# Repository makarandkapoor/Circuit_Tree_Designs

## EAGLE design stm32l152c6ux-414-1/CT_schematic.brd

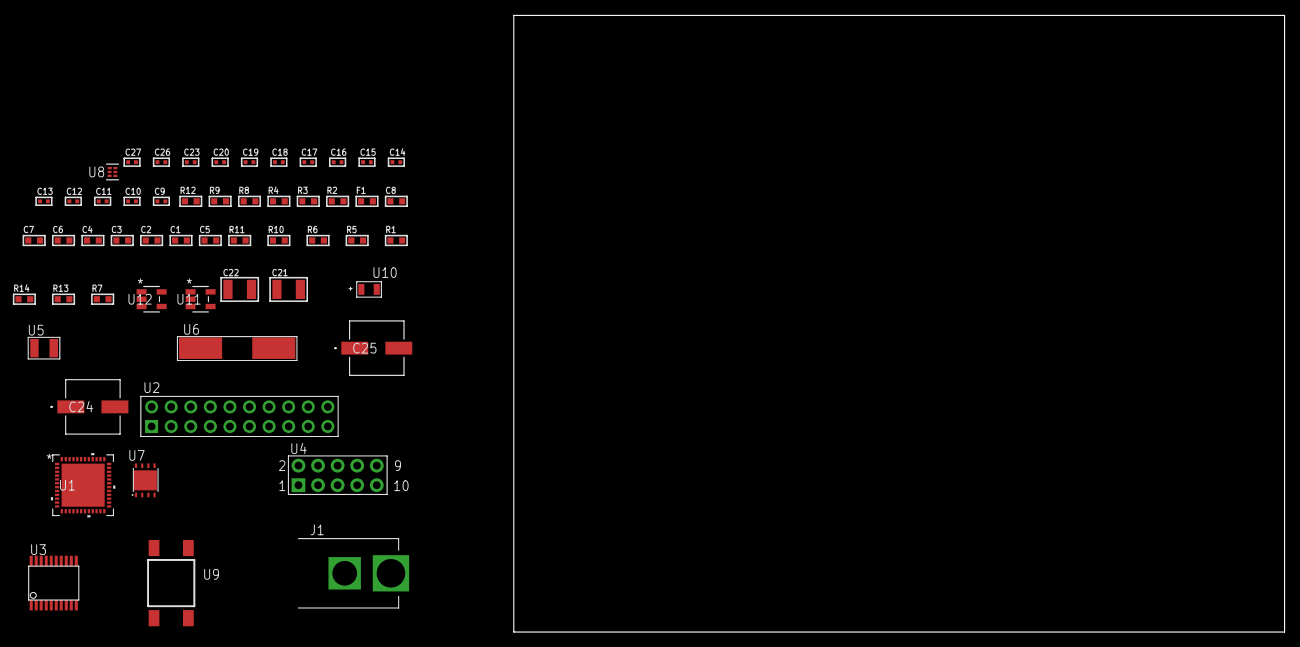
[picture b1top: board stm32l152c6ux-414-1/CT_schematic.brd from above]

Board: 2 copper layers, 100.0 x 80.0 mm, 55 parts (0 on the bottom side), 38 nets, no tracks yet.

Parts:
C1, C2, C3, C4, C6: 1e-07; C0603
C5: 4.7e-06; C0603
C7: 1e-08; C0603
C8: 1e-06; C0603
C9, C10, C11, C12: 1e-11; C0402
C13, C14, C15, C16, C17, C18, C19, C23: 1e-07; C0402
C20, C26, C27: 1e-08; C0402
C21, C22: 1e-05; C1210
C24, C25: 0.0001; EXV-9H
F1: 240.0; L0603
J1: PJ-037B; PJ-037B_PACKAGE
R1, R5, R6, R10, R11: 10000.0; R0603
R2, R9: 1000.0; R0603
R3: 1600.5; R0603
R4: 4700.0; R0603
R7: 100000.0; R0603
R8: 2231.0; R0603
R12: 9100.0; R0603
R13: 680000.0; R0603
R14: 120000.0; R0603
U1: STM32L152C6U6; UFQFPN48
U2: TST-110-05-T-D-RA
U3: SP3203ECY-L/TR; TSSOP20-I
U4: HTSS-105-01-G-D
U5: ABS07-32.768KHZ-7-T
U6: ABLS-25.000MHZ-B2F-T
U7: LP3878SDX-ADJ/NOPB; WSON-8
U8: TPS3895ADRYR; SON-6
U9: 4-1437565-2; SW_4-1437565-2
U10: Q65110A2395; LGM67K-G1J2-24-Z
U11, U12: nc7sz125m5x; NC7SZ125M5X

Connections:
CLK_CRYSTAL_U1_3: C9.1, U1.3, U5.1
CLK_CRYSTAL_U1_4: C10.1, U1.4, U5.2
CLK_CRYSTAL_U1_5: C11.1, U1.5, U6.1
CLK_CRYSTAL_U1_6: C12.1, U1.6, U6.2
GND: C1.2, C2.2, C3.2, C4.2, C5.2, C6.2, C7.2, C8.2, C9.2, C10.2, C11.2, C12.2, C13.2, C14.2, C15.2, C18.2, C19.2, C20.2, C21.2, C22.2, C23.2, C24.2, C25.2, C26.2, C27.2, J1.2, R2.2, R5.2, R9.2, R12.2, R14.2, U1.8, U1.23, U1.35, U1.47, U1.49, U2.4, U2.6, U2.8, U2.10, U2.12, U2.14, U2.16, U2.18, U2.20, U3.18, U4.9, U7.3, U7.PAD, U8.2, U10.C, U11.2, U11.3, U12.1, U12.3
NET_U1_1: C6.1, U1.1
NET_U1_7: R4.1, U1.7, U12.4
NET_U1_9: C7.1, C8.1, F1.1, U1.9
NET_U1_44: R5.1, U1.44
NET_U1_45: R3.1, U1.45, U10.A
NET_U1_46: R1.1, U1.46, U9.3, U9.4
NET_U3_1: C16.1, U3.1
NET_U3_2: C18.1, U3.2
NET_U3_3: C16.2, U3.3
NET_U3_4: C17.1, U3.4
NET_U3_5: C17.2, U3.5
NET_U3_6: C19.1, U3.6
NET_U4_3: U3.14, U4.3
NET_U4_4: U3.13, U4.4
NET_U4_5: U3.17, U4.5
NET_U4_6: U3.16, U4.6
NET_U7_1: C20.1, U7.1
NET_U7_6: R8.2, R9.1, U7.6
NET_U7_8: R7.1, U7.8
NET_U8_1: R11.1, R12.1, U8.1
NET_U8_3: R13.2, R14.1, U8.3
NET_U8_4: R10.1, U8.4, U11.4, U12.2
NET_U9_1: R2.1, U9.1, U9.2
PROC_SYS_JTCK_SWCLK: U1.37, U2.9
PROC_SYS_JTDO_TRACESWO: U1.39, U2.13
PROC_SYS_JTMS_SWDIO: U1.34, U2.7
PROC_USART1_CTS: U1.32, U3.8
PROC_USART1_RTS: U1.33, U3.10
PROC_USART1_RX: U1.31, U3.11
PROC_USART1_TX: U1.30, U3.7
RST_OUT_U2_SRESET_B: R6.1, U2.15, U11.1
VCC_S1_13V5: C21.1, C24.1, C25.1, J1.1, R7.2, U7.4
VCC_TIER1_3V3: C1.1, C2.1, C3.1, C4.1, C5.1, C13.1, C14.1, C15.1, C22.1, C23.1, C26.1, C27.1, F1.2, R1.2, R3.2, R4.2, R6.2, R8.1, R10.2, R11.2, R13.1, U1.24, U1.36, U1.48, U2.1, U3.12, U3.19, U7.5, U8.6, U11.5, U12.5

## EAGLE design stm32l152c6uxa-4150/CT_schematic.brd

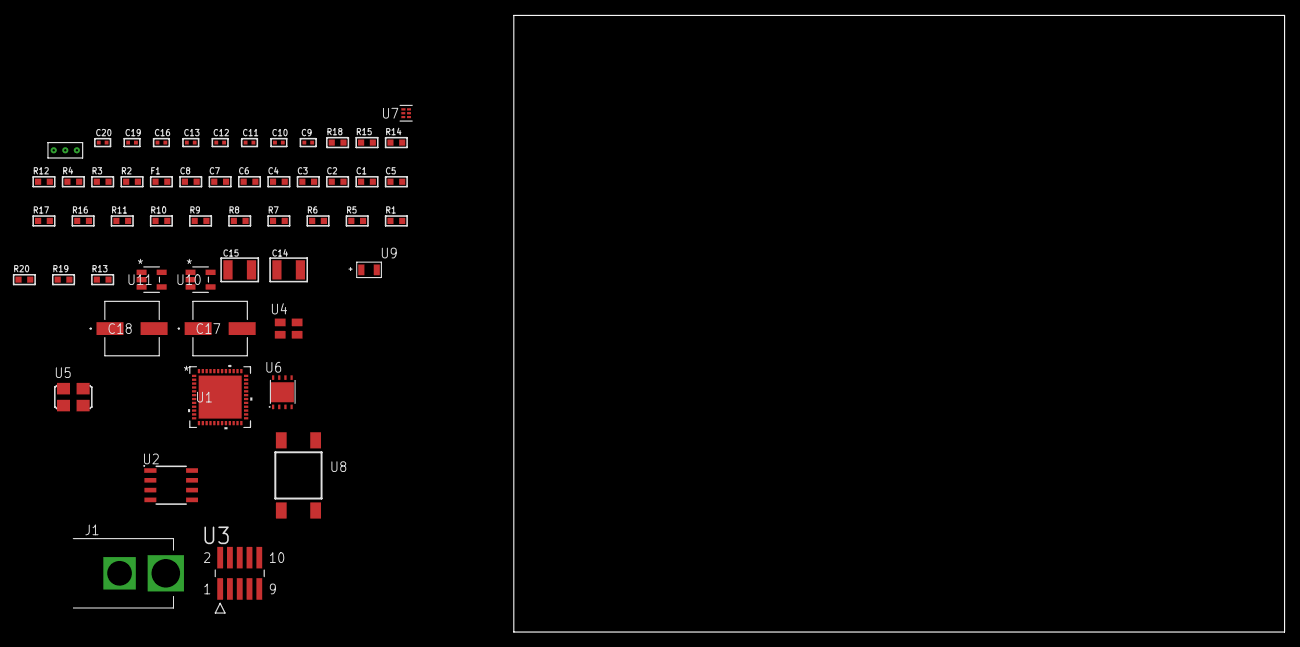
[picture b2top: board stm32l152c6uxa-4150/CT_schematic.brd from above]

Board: 2 copper layers, 100.0 x 80.0 mm, 54 parts (0 on the bottom side), 31 nets, no tracks yet.

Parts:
C1, C2, C3, C4, C6: 1e-07; C0603
C5: 4.7e-06; C0603
C7: 1e-08; C0603
C8: 1e-06; C0603
C9, C11, C12, C13, C19, C20: 1e-08; C0402
C10, C16: 1e-07; C0402
C14, C15: 1e-05; C1210
C17, C18: 0.0001; EXV-9H
F1: 240.0; L0603
J1: PJ-037B; PJ-037B_PACKAGE
R1, R5, R6, R7, R8, R9, R10, R11, R16, R17: 10000.0; R0603
R2, R15: 1000.0; R0603
R3: 1600.5; R0603
R4: 4700.0; R0603
R12: 5.0; R0603
R13: 100000.0; R0603
R14: 2231.0; R0603
R18: 9100.0; R0603
R19: 680000.0; R0603
R20: 120000.0; R0603
U1: STM32L152C6U6A; UFQFPN48
U2: AT25160B-SSHL-T; SOIC-8
U3: FTSH-105-01-L-DV-K; SAMTEC_FTSH-105-01-L-DV-K
U4: ASEK-32.768KHz-ECST; ASEK
U5: ASFL1-25MHZ-NCS; ASFL1
U6: LP3878SDX-ADJ/NOPB; WSON-8
U7: TPS3895ADRYR; SON-6
U8: 4-1437565-2; SW_4-1437565-2
U9: Q65110A2395; LGM67K-G1J2-24-Z
U10, U11: nc7sz125m5x; NC7SZ125M5X
U12: Dummy; DUMMY_PACKAGE_113

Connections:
CLK_U1_3: U1.3, U4.3
CLK_U1_5: U1.5, U5.3
GND: C1.2, C2.2, C3.2, C4.2, C5.2, C6.2, C7.2, C8.2, C9.2, C10.2, C11.2, C12.2, C13.2, C14.2, C15.2, C16.2, C17.2, C18.2, C19.2, C20.2, J1.2, R2.2, R5.2, R12.2, R15.2, R18.2, R20.2, U1.8, U1.23, U1.35, U1.47, U1.49, U2.4, U3.3, U3.5, U4.2, U5.2, U6.3, U6.PAD, U7.2, U9.C, U10.2, U10.3, U11.1, U11.3, U12.1
NET_U1_1: C6.1, U1.1
NET_U1_7: R4.1, U1.7, U11.4
NET_U1_9: C7.1, C8.1, F1.1, U1.9
NET_U1_44: R5.1, U1.44
NET_U1_45: R3.1, U1.45, U9.A
NET_U1_46: R1.1, U1.46, U8.3, U8.4
NET_U2_3: R6.1, U2.3
NET_U2_7: R8.1, U2.7
NET_U3_9: R12.1, U3.9
NET_U6_1: C13.1, U6.1
NET_U6_6: R14.2, R15.1, U6.6
NET_U6_8: R13.1, U6.8
NET_U7_1: R17.1, R18.1, U7.1
NET_U7_3: R19.2, R20.1, U7.3
NET_U7_4: R16.1, U7.4, U10.4, U11.2
NET_U8_1: R2.1, U8.1, U8.2
PROC_ADC_IN19: U1.26, U12.3
PROC_ADC_IN20: U1.27, U12.2
PROC_SPI1_MISO: U1.16, U2.2
PROC_SPI1_MOSI: U1.17, U2.5
PROC_SPI1_NSS: R7.1, U1.14, U2.1
PROC_SPI1_SCK: U1.15, U2.6
PROC_SYS_JTCK_SWCLK: R10.1, U1.37, U3.4
PROC_SYS_JTDO_TRACESWO: U1.39, U3.6
PROC_SYS_JTMS_SWDIO: R11.1, U1.34, U3.2
RST_OUT_U3_JTAG_RST_B: R9.1, U3.10, U10.1
VCC_S1_11V2: C14.1, C17.1, C18.1, J1.1, R13.2, U6.4
VCC_TIER1_3V3: C1.1, C2.1, C3.1, C4.1, C5.1, C9.1, C10.1, C11.1, C12.1, C15.1, C16.1, C19.1, C20.1, F1.2, R1.2, R3.2, R4.2, R6.2, R7.2, R8.2, R9.2, R10.2, R11.2, R14.1, R16.2, R17.2, R19.1, U1.24, U1.36, U1.48, U2.8, U3.1, U4.4, U5.4, U6.5, U7.6, U10.5, U11.5

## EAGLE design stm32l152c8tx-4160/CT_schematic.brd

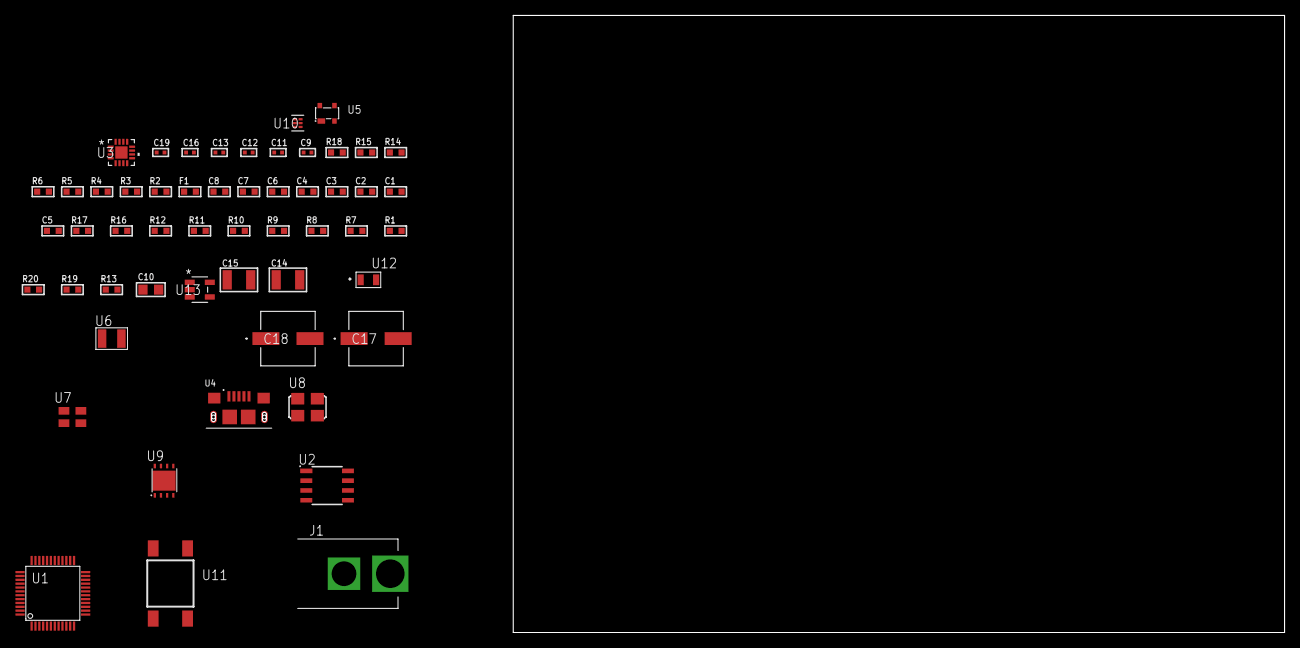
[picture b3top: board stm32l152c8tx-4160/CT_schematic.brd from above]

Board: 2 copper layers, 54 parts (0 on the bottom side), 33 nets, no tracks yet.

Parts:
C1, C2, C3, C4, C6: 1e-07; C0603
C5: 4.7e-06; C0603
C7: 1e-08; C0603
C8: 1e-06; C0603
C9, C11, C12, C13, C19: 1e-08; C0402
C10: 4.7e-06; C0805
C14, C15: 1e-05; C1210
C16: 1e-07; C0402
C17, C18: 0.0001; EXV-9H
F1: 240.0; L0603
J1: PJ-037B; PJ-037B_PACKAGE
R1, R7, R8, R9, R10, R11, R12, R16, R17: 10000.0; R0603
R2, R15: 1000.0; R0603
R3: 1600.5; R0603
R4: 4700.0; R0603
R5, R6: 2200.0; R0603
R13: 100000.0; R0603
R14: 2231.0; R0603
R18: 9100.0; R0603
R19: 680000.0; R0603
R20: 120000.0; R0603
U1: STM32L152C8T6; LQFP48
U2: AT25128B-SSHL-T; SOIC-8
U3: M41T65Q6F; M41T65_QFN-16
U4: 10118193-0001LF; FCI_10118193-0001LF
U5: prtr5v0u2ax; SOT143B
U6: ABS07-32.768KHZ-7-T
U7: ASEK-32.768KHz-ECST; ASEK
U8: ASFL1-25MHZ-NCS; ASFL1
U9: LP3878SDX-ADJ/NOPB; WSON-8
U10: TPS3895ADRYR; SON-6
U11: 4-1437565-2; SW_4-1437565-2
U12: Q65110A2395; LGM67K-G1J2-24-Z
U13: nc7sz125m5x; NC7SZ125M5X

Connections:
CLK_CRYSTAL_U3_1: U3.1, U6.1
CLK_CRYSTAL_U3_2: U3.2, U6.2
CLK_U1_3: U1.3, U7.3
CLK_U1_5: U1.5, U8.3
GND: C1.2, C2.2, C3.2, C4.2, C5.2, C6.2, C7.2, C8.2, C9.2, C10.2, C11.2, C12.2, C13.2, C14.2, C15.2, C16.2, C17.2, C18.2, C19.2, J1.2, R2.2, R7.2, R15.2, R18.2, R20.2, U1.8, U1.23, U1.35, U1.47, U2.4, U3.3, U3.5, U3.17, U4.5, U4.6, U4.7, U4.8, U4.9, U5.1, U7.2, U8.2, U9.3, U9.PAD, U10.2, U12.C, U13.1, U13.3
NET_U1_1: C6.1, U1.1
NET_U1_7: R4.1, U1.7, U13.4
NET_U1_9: C7.1, C8.1, F1.1, U1.9
NET_U1_42: R5.1, U1.42, U3.10
NET_U1_43: R6.1, U1.43, U3.9
NET_U1_44: R7.1, U1.44
NET_U1_45: R3.1, U1.45, U12.A
NET_U1_46: R1.1, U1.46, U11.3, U11.4
NET_U2_3: R8.1, U2.3
NET_U2_7: R10.1, U2.7
NET_U3_4: R11.1, U3.4
NET_U3_11: R12.1, U3.11
NET_U5_4: U4.1, U5.4
NET_U9_1: C13.1, U9.1
NET_U9_6: R14.2, R15.1, U9.6
NET_U9_8: R13.1, U9.8
NET_U10_1: R17.1, R18.1, U10.1
NET_U10_3: R19.2, R20.1, U10.3
NET_U10_4: R16.1, U10.4, U13.2
NET_U11_1: R2.1, U11.1, U11.2
PROC_SPI1_MISO: U1.16, U2.2
PROC_SPI1_MOSI: U1.17, U2.5
PROC_SPI1_NSS: R9.1, U1.14, U2.1
PROC_SPI1_SCK: U1.15, U2.6
PROC_USB_DM: U1.32, U4.2, U5.3
PROC_USB_DP: U1.33, U4.3, U5.2
VCC_S1_11V3: C14.1, C17.1, C18.1, J1.1, R13.2, U9.4
VCC_TIER1_3V3: C1.1, C2.1, C3.1, C4.1, C5.1, C9.1, C10.1, C11.1, C12.1, C15.1, C16.1, C19.1, F1.2, R1.2, R3.2, R4.2, R5.2, R6.2, R8.2, R9.2, R10.2, R11.2, R12.2, R14.1, R16.2, R17.2, R19.1, U1.24, U1.36, U1.48, U2.8, U3.14, U7.4, U8.4, U9.5, U10.6, U13.5

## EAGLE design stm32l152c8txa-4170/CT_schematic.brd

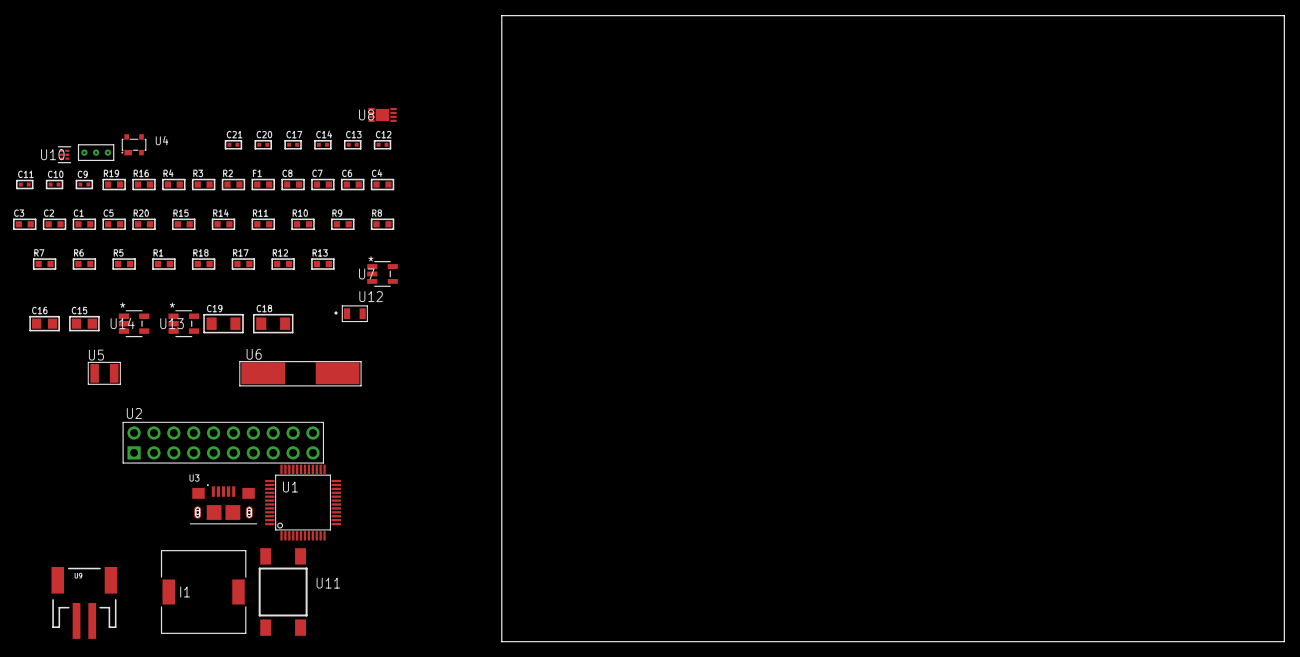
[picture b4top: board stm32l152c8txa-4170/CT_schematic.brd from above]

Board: 2 copper layers, 58 parts (0 on the bottom side), 34 nets, no tracks yet.

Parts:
C1, C2, C3, C4, C6: 1e-07; C0603
C5: 4.7e-06; C0603
C7: 1e-08; C0603
C8: 1e-06; C0603
C9, C10, C11, C12: 1e-11; C0402
C13, C14, C17: 1e-07; C0402
C15, C16: 1e-05; C0805
C18, C19: 1e-05; C1206
C20, C21: 1e-08; C0402
F1: 240.0; L0603
I1: 3.8e-06; DR1040
R1, R5, R6, R7, R8, R9, R10, R11, R14, R15, R20: 10000.0; R0603
R2: 1000.0; R0603
R3: 1600.5; R0603
R4: 4700.0; R0603
R12: 220000.0; R0603
R13: 1000000.0; R0603
R16: 9100.0; R0603
R17: 680000.0; R0603
R18: 120000.0; R0603
R19: 2000.0; R0603
U1: STM32L152C8T6A; LQFP48
U2: TST-110-05-T-D-RA
U3: 10118193-0001LF; FCI_10118193-0001LF
U4: prtr5v0u2ax; SOT143B
U5: ABS07-32.768KHZ-7-T
U6: ABLS-25.000MHZ-B2F-T
U7: ltc3406es5; TSOT-23-5
U8: MCP73831T-2ACI/MC; DFN8_2X3MC
U9: S2B-PH-SM4-TB(LF)(SN); JST-2-SMD
U10: TPS3895ADRYR; SON-6
U11: 4-1437565-2; SW_4-1437565-2
U12: Q65110A2395; LGM67K-G1J2-24-Z
U13, U14: nc7sz125m5x; NC7SZ125M5X
U15: Dummy; DUMMY_PACKAGE_119

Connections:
CLK_CRYSTAL_U1_3: C9.1, U1.3, U5.1
CLK_CRYSTAL_U1_4: C10.1, U1.4, U5.2
CLK_CRYSTAL_U1_5: C11.1, U1.5, U6.1
CLK_CRYSTAL_U1_6: C12.1, U1.6, U6.2
GND: C1.2, C2.2, C3.2, C4.2, C5.2, C6.2, C7.2, C8.2, C9.2, C10.2, C11.2, C12.2, C13.2, C14.2, C15.2, C16.1, C16.2, C17.2, C18.2, C19.2, C20.2, C21.2, R2.2, R5.2, R11.2, R12.2, R16.2, R18.2, R19.2, U1.8, U1.23, U1.35, U1.47, U2.4, U2.6, U2.8, U2.10, U2.12, U2.14, U2.16, U2.18, U2.20, U3.5, U3.6, U3.7, U3.8, U3.9, U4.1, U7.2, U8.6, U8.9, U9.2, U10.2, U12.C, U13.2, U13.3, U14.1, U14.3, U15.1
INPUT_USBPOWER_5V: C18.1, R20.2, U3.1, U4.4, U8.1, U8.2
NET_U1_1: C6.1, U1.1
NET_U1_7: R4.1, U1.7, U14.4
NET_U1_9: C7.1, C8.1, F1.1, U1.9
NET_U1_44: R5.1, U1.44
NET_U1_45: R3.1, U1.45, U12.A
NET_U1_46: R1.1, U1.46, U11.3, U11.4
NET_U2_19: R11.1, U2.19
NET_U7_3: I1.1, U7.3
NET_U7_5: R12.1, R13.1, U7.5
NET_U7_ATNET_3: I1.2, R13.2
NET_U8_5: R20.1, U8.5
NET_U8_8: R19.1, U8.8
NET_U10_1: R15.1, R16.1, U10.1
NET_U10_3: R17.2, R18.1, U10.3
NET_U10_4: R14.1, U10.4, U13.4, U14.2
NET_U11_1: R2.1, U11.1, U11.2
PROC_SYS_JTCK_SWCLK: R9.1, U1.37, U2.9
PROC_SYS_JTDI: R7.1, U1.38, U2.5
PROC_SYS_JTDO_TRACESWO: U1.39, U2.13
PROC_SYS_JTMS_SWDIO: R8.1, U1.34, U2.7
PROC_SYS_JTRST: R6.1, U1.40, U2.3
PROC_TIM10_CH1: U1.16, U15.2
PROC_TIM11_CH1: U1.17, U15.3
PROC_USB_DM: U1.32, U3.2, U4.3
PROC_USB_DP: U1.33, U3.3, U4.2
RST_OUT_U2_SRESET_B: R10.1, U2.15, U13.1
VCC_S1_3V7: C15.1, C19.1, U7.4, U8.3, U8.4, U9.1
VCC_TIER1_3V3: C1.1, C2.1, C3.1, C4.1, C5.1, C13.1, C14.1, C16.2, C17.1, C20.1, C21.1, F1.2, I1.2, R1.2, R3.2, R4.2, R6.2, R7.2, R8.2, R9.2, R10.2, R13.2, R14.2, R15.2, R17.1, U1.24, U1.36, U1.48, U2.1, U2.2, U10.6, U13.5, U14.5

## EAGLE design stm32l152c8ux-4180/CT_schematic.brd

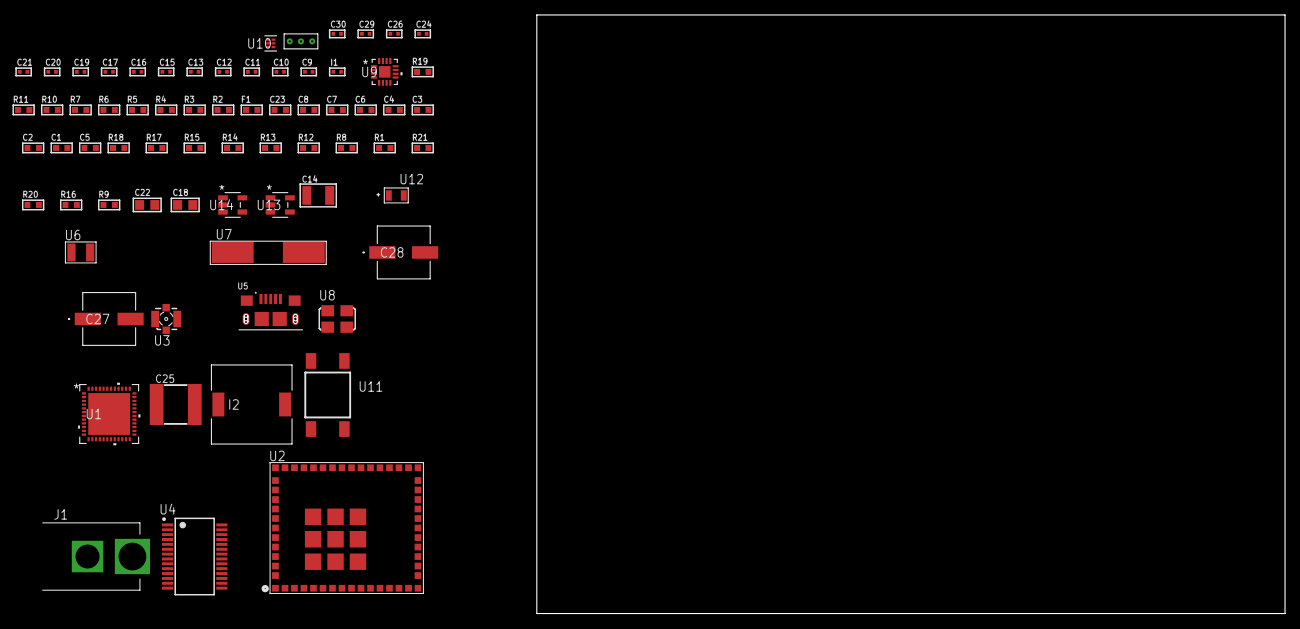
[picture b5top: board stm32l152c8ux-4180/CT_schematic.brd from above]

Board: 2 copper layers, 70 parts (0 on the bottom side), 42 nets, no tracks yet.

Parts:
C1, C2, C3, C4, C6: 1e-07; C0603
C5: 4.7e-06; C0603
C7: 1e-08; C0603
C8, C23: 1e-06; C0603
C9, C10, C11, C12: 1e-11; C0402
C13: 1e-12; C0402
C14: 2.2e-05; C1210
C15, C16, C17, C19, C20, C24, C26: 1e-07; C0402
C18: 4.7e-06; C0805
C21, C29, C30: 1e-08; C0402
C22: 1e-05; C0805
C25: 6.8e-05; 2220
C27, C28: 0.0001; EXV-9H
F1: 240.0; L0603
I1: 3.6e-09; C0402
I2: 5.2e-06; DR1040
J1: PJ-037B; PJ-037B_PACKAGE
R1, R8, R12, R13, R17, R18: 10000.0; R0603
R2: 1000.0; R0603
R3: 1600.5; R0603
R4, R5, R11: 4700.0; R0603
R6, R7: 2200.0; R0603
R9: 100000.0; R0603
R10: 2700.0; R0603
R14: 20000.0; R0603
R15: 91000.0; R0603
R16: 300000.0; R0603
R19: 9100.0; R0603
R20: 680000.0; R0603
R21: 120000.0; R0603
U1: STM32L152C8U6; UFQFPN48
U2: CC3200MODR1M2AMOBT; LGA63S127P16X13_2050X1750X150
U3: 73412-0114; COAXIAL_C
U4: FT232RL-REEL; SSOP-28
U5: 10118193-0001LF; FCI_10118193-0001LF
U6: ABS07-32.768KHZ-7-T
U7: ABLS-25.000MHZ-B2F-T
U8: ASFL1-12MHZ-NCS; ASFL1
U9: LTC3601EUD#PBF; QFN-16_EP
U10: TPS3895ADRYR; SON-6
U11: 4-1437565-2; SW_4-1437565-2
U12: Q65110A2395; LGM67K-G1J2-24-Z
U13, U14: nc7sz125m5x; NC7SZ125M5X
U15: Dummy; DUMMY_PACKAGE_144

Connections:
CLK_CRYSTAL_U1_3: C9.1, U1.3, U6.1
CLK_CRYSTAL_U1_4: C10.1, U1.4, U6.2
CLK_CRYSTAL_U1_5: C11.1, U1.5, U7.1
CLK_CRYSTAL_U1_6: C12.1, U1.6, U7.2
CLK_U4_27: U4.27, U8.3
GND: C1.2, C2.2, C3.2, C4.2, C5.2, C6.2, C7.2, C8.2, C9.2, C10.2, C11.2, C12.2, C13.2, C14.2, C15.2, C16.2, C17.2, C18.2, C19.2, C20.2, C21.2, C22.2, C23.2, C25.1, C25.2, C26.2, C27.2, C28.2, C29.2, C30.2, J1.2, R2.2, R8.2, R9.2, R10.2, R13.2, R14.2, R16.2, R19.2, R21.2, U1.8, U1.23, U1.35, U1.47, U1.49, U2.1, U2.2, U2.16, U2.27, U2.28, U2.30, U2.32, U2.38, U2.43, U2.55, U2.56, U2.57, U2.58, U2.59, U2.60, U2.61, U2.62, U2.63, U3.1, U3.2, U3.3, U3.4, U4.7, U4.18, U4.21, U4.25, U4.26, U5.5, U5.6, U5.7, U5.8, U5.9, U8.2, U9.1, U9.9, U9.17, U10.2, U12.C, U13.1, U13.3, U14.1, U14.3, U15.1
NET_U1_1: C6.1, U1.1
NET_U1_7: R5.1, U1.7, U14.4
NET_U1_9: C7.1, C8.1, F1.1, U1.9
NET_U1_42: R6.1, U1.42, U2.3
NET_U1_43: R7.1, U1.43, U2.4
NET_U1_44: R8.1, U1.44
NET_U1_45: R3.1, U1.45, U12.A
NET_U1_46: R1.1, U1.46, U11.3, U11.4
NET_U2_21: R9.1, U2.21
NET_U2_23: R10.1, U2.23
NET_U2_35: R4.1, U2.35, U13.4
NET_U3_1: C13.1, I1.1, U3.1
NET_U4_14: R12.1, U4.14
NET_U4_17: C19.1, U4.17
NET_U4_19: R13.1, U4.19
NET_U5_1: R11.1, U5.1
NET_U5_2: U4.16, U5.2
NET_U5_3: U4.15, U5.3
NET_U9_3: C24.2, I2.1, U9.3, U9.4
NET_U9_6: C24.1, U9.6
NET_U9_7: C23.1, U9.7, U9.12
NET_U9_10: R16.1, U9.10
NET_U9_11: R14.1, R15.1, U9.11
NET_U9_ATNET_3: I2.2, R15.2
NET_U10_1: R18.1, R19.1, U10.1
NET_U10_3: R20.2, R21.1, U10.3
NET_U10_4: R17.1, U10.4, U13.2, U14.2
NET_U11_1: R2.1, U11.1, U11.2
PROC_ADC_IN19: U1.26, U15.3
PROC_ADC_IN20: U1.27, U15.2
PROC_USART1_CTS: U1.32, U4.3
PROC_USART1_RTS: U1.33, U4.11
PROC_USART1_RX: U1.31, U4.1
PROC_USART1_TX: U1.30, U4.5
VCC_S1_11V2: C22.1, C27.1, C28.1, J1.1, U9.15, U9.16
VCC_TIER1_3V3: C1.1, C2.1, C3.1, C4.1, C5.1, C14.1, C15.1, C16.1, C17.1, C18.1, C20.1, C21.1, C25.2, C26.1, C29.1, C30.1, F1.2, I2.2, R1.2, R3.2, R4.2, R5.2, R6.2, R7.2, R12.2, R15.2, R17.2, R18.2, R20.1, U1.24, U1.36, U1.48, U2.36, U2.37, U2.40, U4.4, U4.20, U8.4, U9.8, U10.6, U13.5, U14.5

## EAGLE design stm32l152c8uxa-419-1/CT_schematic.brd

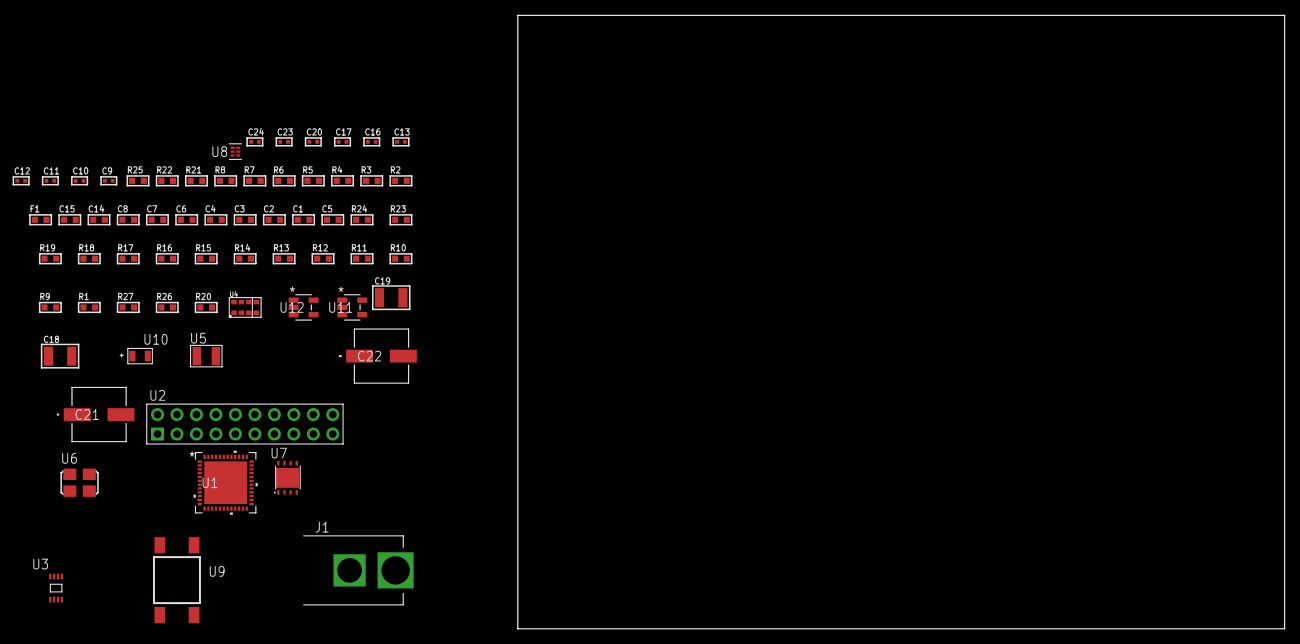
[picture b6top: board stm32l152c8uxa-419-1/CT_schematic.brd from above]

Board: 2 copper layers, 100.0 x 80.0 mm, 65 parts (0 on the bottom side), 34 nets, no tracks yet.

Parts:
C1, C2, C3, C4, C6: 1e-07; C0603
C5: 4.7e-06; C0603
C7: 1e-08; C0603
C8, C14, C15: 1e-06; C0603
C9, C10: 1e-11; C0402
C11, C12, C20: 1e-07; C0402
C13, C16, C17, C23, C24: 1e-08; C0402
C18, C19: 1e-05; C1210
C21, C22: 0.0001; EXV-9H
F1: 240.0; L0603
J1: PJ-037B; PJ-037B_PACKAGE
R1, R9, R10, R11, R12, R13, R14, R15, R16, R17, R18, R19, R23, R24: 10000.0; R0603
R2, R22: 1000.0; R0603
R3: 1600.5; R0603
R4: 4700.0; R0603
R5, R6, R7, R8: 2200.0; R0603
R20: 100000.0; R0603
R21: 2231.0; R0603
R25: 9100.0; R0603
R26: 680000.0; R0603
R27: 120000.0; R0603
U1: STM32L152C8U6A; UFQFPN48
U2: TST-110-05-T-D-RA
U3: 24AA128T-I/MNY; TDFN-8/6MM
U4: TMD27711; SMD-8
U5: ABS07-32.768KHZ-7-T
U6: ASFL1-25MHZ-NCS; ASFL1
U7: LP3878SDX-ADJ/NOPB; WSON-8
U8: TPS3895ADRYR; SON-6
U9: 4-1437565-2; SW_4-1437565-2
U10: Q65110A2395; LGM67K-G1J2-24-Z
U11, U12: nc7sz125m5x; NC7SZ125M5X

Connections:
CLK_CRYSTAL_U1_3: C9.1, U1.3, U5.1
CLK_CRYSTAL_U1_4: C10.1, U1.4, U5.2
CLK_U1_5: U1.5, U6.3
GND: C1.2, C2.2, C3.2, C4.2, C5.2, C6.2, C7.2, C8.2, C9.2, C10.2, C11.2, C12.2, C13.2, C14.2, C15.2, C16.2, C17.2, C18.2, C19.2, C20.2, C21.2, C22.2, C23.2, C24.2, J1.2, R2.2, R9.2, R15.2, R17.2, R18.2, R22.2, R25.2, R27.2, U1.8, U1.23, U1.35, U1.47, U1.49, U2.4, U2.6, U2.8, U2.10, U2.12, U2.14, U2.16, U2.18, U2.20, U3.4, U3.7, U4.3, U6.2, U7.3, U7.PAD, U8.2, U10.C, U11.2, U11.3, U12.1, U12.3
NET_U1_1: C6.1, U1.1
NET_U1_7: R4.1, U1.7, U12.4
NET_U1_9: C7.1, C8.1, F1.1, U1.9
NET_U1_21: R7.1, U1.21, U3.6
NET_U1_22: R8.1, U1.22, U3.5
NET_U1_42: R5.1, U1.42, U4.2
NET_U1_43: R6.1, U1.43, U4.8
NET_U1_44: R9.1, U1.44
NET_U1_45: R3.1, U1.45, U10.A
NET_U1_46: R1.1, U1.46, U9.3, U9.4
NET_U2_19: R15.1, U2.19
NET_U3_1: R16.1, U3.1
NET_U3_2: R17.1, U3.2
NET_U3_3: R18.1, U3.3
NET_U4_7: R19.1, U4.7
NET_U7_1: C17.1, U7.1
NET_U7_6: R21.2, R22.1, U7.6
NET_U7_8: R20.1, U7.8
NET_U8_1: R24.1, R25.1, U8.1
NET_U8_3: R26.2, R27.1, U8.3
NET_U8_4: R23.1, U8.4, U11.4, U12.2
NET_U9_1: R2.1, U9.1, U9.2
PROC_SYS_JTCK_SWCLK: R13.1, U1.37, U2.9
PROC_SYS_JTDI: R11.1, U1.38, U2.5
PROC_SYS_JTDO_TRACESWO: U1.39, U2.13
PROC_SYS_JTMS_SWDIO: R12.1, U1.34, U2.7
PROC_SYS_JTRST: R10.1, U1.40, U2.3
RST_OUT_U2_SRESET_B: R14.1, U2.15, U11.1
VCC_S1_12V5: C18.1, C21.1, C22.1, J1.1, R20.2, U7.4
VCC_TIER1_3V3: C1.1, C2.1, C3.1, C4.1, C5.1, C11.1, C12.1, C13.1, C14.1, C15.1, C16.1, C19.1, C20.1, C23.1, C24.1, F1.2, R1.2, R3.2, R4.2, R5.2, R6.2, R7.2, R8.2, R10.2, R11.2, R12.2, R13.2, R14.2, R16.2, R19.2, R21.1, R23.2, R24.2, R26.1, U1.24, U1.36, U1.48, U2.1, U2.2, U3.8, U4.1, U4.4, U6.4, U7.5, U8.6, U11.5, U12.5

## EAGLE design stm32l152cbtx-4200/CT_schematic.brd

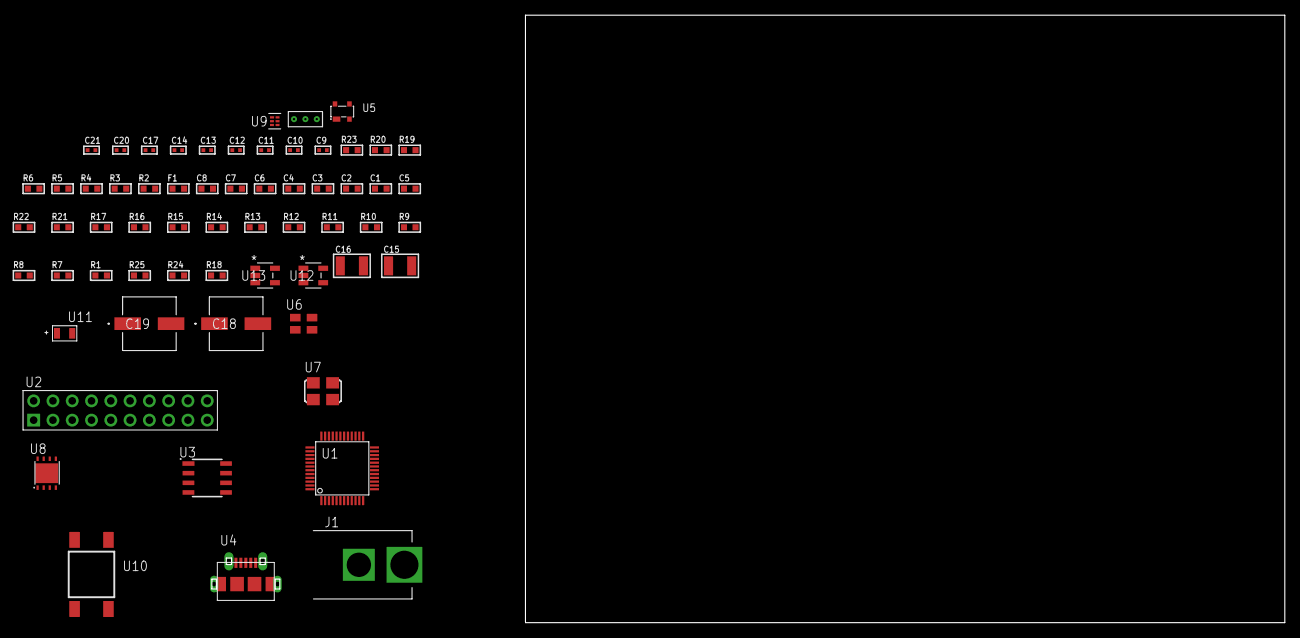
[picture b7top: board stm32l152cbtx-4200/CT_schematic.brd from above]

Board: 2 copper layers, 62 parts (0 on the bottom side), 36 nets, no tracks yet.

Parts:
C1, C2, C3, C4, C6: 1e-07; C0603
C5: 4.7e-06; C0603
C7: 1e-08; C0603
C8: 1e-06; C0603
C9, C10, C17: 1e-07; C0402
C11, C12, C13, C14, C20, C21: 1e-08; C0402
C15, C16: 1e-05; C1210
C18, C19: 0.0001; EXV-9H
F1: 240.0; L0603
J1: PJ-037B; PJ-037B_PACKAGE
R1, R7, R8, R9, R10, R11, R12, R13, R14, R15, R16, R17, R21, R22: 10000.0; R0603
R2, R20: 1000.0; R0603
R3: 1600.5; R0603
R4: 4700.0; R0603
R5, R6: 2200.0; R0603
R18: 100000.0; R0603
R19: 2231.0; R0603
R23: 9100.0; R0603
R24: 680000.0; R0603
R25: 120000.0; R0603
U1: STM32L152CBT6; LQFP48
U2: TST-110-05-T-D-RA
U3: AT24C02D-SSHM-T; AT24C02D
U4: 47590-0001; MICRO_USB_AB
U5: prtr5v0u2ax; SOT143B
U6: ASEK-32.768KHz-ECST; ASEK
U7: ASFL1-25MHZ-NCS; ASFL1
U8: LP3878SDX-ADJ/NOPB; WSON-8
U9: TPS3895ADRYR; SON-6
U10: 4-1437565-2; SW_4-1437565-2
U11: Q65110A2395; LGM67K-G1J2-24-Z
U12, U13: nc7sz125m5x; NC7SZ125M5X
U14: Dummy; DUMMY_PACKAGE_131

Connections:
CLK_U1_3: U1.3, U6.3
CLK_U1_5: U1.5, U7.3
GND: C1.2, C2.2, C3.2, C4.2, C5.2, C6.2, C7.2, C8.2, C9.2, C10.2, C11.2, C12.2, C13.2, C14.2, C15.2, C16.2, C17.2, C18.2, C19.2, C20.2, C21.2, J1.2, R2.2, R7.2, R13.2, R14.2, R16.2, R17.2, R20.2, R23.2, R25.2, U1.8, U1.23, U1.35, U1.47, U2.4, U2.6, U2.8, U2.10, U2.12, U2.14, U2.16, U2.18, U2.20, U3.4, U4.5, U4.6, U4.7, U4.8, U4.9, U5.1, U6.2, U7.2, U8.3, U8.PAD, U9.2, U11.C, U12.2, U12.3, U13.1, U13.3, U14.1
NET_U1_1: C6.1, U1.1
NET_U1_7: R4.1, U1.7, U13.4
NET_U1_9: C7.1, C8.1, F1.1, U1.9
NET_U1_42: R5.1, U1.42, U3.6
NET_U1_43: R6.1, U1.43, U3.5
NET_U1_44: R7.1, U1.44
NET_U1_45: R3.1, U1.45, U11.A
NET_U1_46: R1.1, U1.46, U10.3, U10.4
NET_U2_19: R13.1, U2.19
NET_U3_1: R15.1, U3.1
NET_U3_2: R16.1, U3.2
NET_U3_3: R17.1, U3.3
NET_U3_7: R14.1, U3.7
NET_U5_4: U4.1, U5.4
NET_U8_1: C14.1, U8.1
NET_U8_6: R19.2, R20.1, U8.6
NET_U8_8: R18.1, U8.8
NET_U9_1: R22.1, R23.1, U9.1
NET_U9_3: R24.2, R25.1, U9.3
NET_U9_4: R21.1, U9.4, U12.4, U13.2
NET_U10_1: R2.1, U10.1, U10.2
PROC_PC13_WKUP2: U1.2, U14.2
PROC_PC15_OSC32_OUT: U1.4, U14.3
PROC_SYS_JTCK_SWCLK: R11.1, U1.37, U2.9
PROC_SYS_JTDI: R9.1, U1.38, U2.5
PROC_SYS_JTDO_TRACESWO: U1.39, U2.13
PROC_SYS_JTMS_SWDIO: R10.1, U1.34, U2.7
PROC_SYS_JTRST: R8.1, U1.40, U2.3
PROC_USB_DM: U1.32, U4.2, U5.3
PROC_USB_DP: U1.33, U4.3, U5.2
RST_OUT_U2_SRESET_B: R12.1, U2.15, U12.1
VCC_S1_13V8: C15.1, C18.1, C19.1, J1.1, R18.2, U8.4
VCC_TIER1_3V3: C1.1, C2.1, C3.1, C4.1, C5.1, C9.1, C10.1, C11.1, C12.1, C13.1, C16.1, C17.1, C20.1, C21.1, F1.2, R1.2, R3.2, R4.2, R5.2, R6.2, R8.2, R9.2, R10.2, R11.2, R12.2, R15.2, R19.1, R21.2, R22.2, R24.1, U1.24, U1.36, U1.48, U2.1, U2.2, U3.8, U6.4, U7.4, U8.5, U9.6, U12.5, U13.5

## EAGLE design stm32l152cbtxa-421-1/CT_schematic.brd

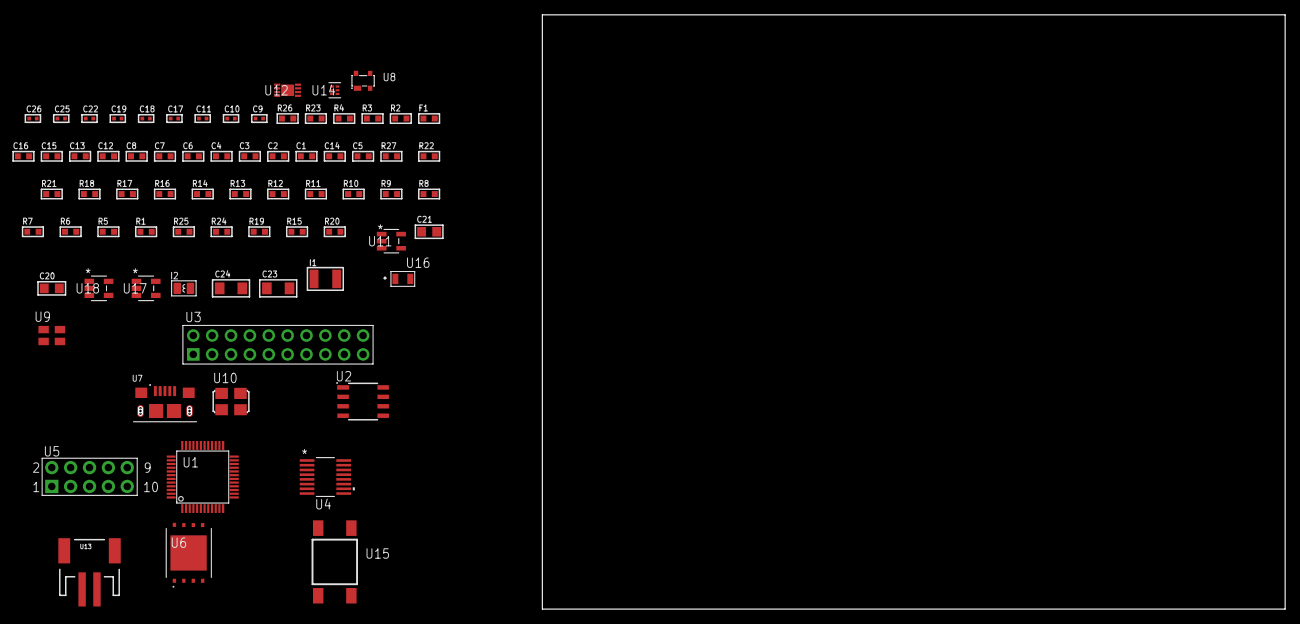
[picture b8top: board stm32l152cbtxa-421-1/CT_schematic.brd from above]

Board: 2 copper layers, 74 parts (0 on the bottom side), 55 nets, no tracks yet.

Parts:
C1, C2, C3, C4, C6: 1e-07; C0603
C5: 4.7e-06; C0603
C7: 1e-08; C0603
C8, C12, C13, C15, C16: 1e-06; C0603
C9, C17, C18, C19, C25, C26: 1e-08; C0402
C10, C11, C22: 1e-07; C0402
C14: 2.2e-07; C0603
C20, C21: 1e-05; C0805
C23, C24: 1e-05; C1206
F1: 240.0; L0603
I1: 1e-05; L1210
I2: 3.3e-06; L0806
R1, R5, R6, R7, R8, R9, R10, R11, R12, R13, R14, R16, R17, R18, R21, R22, R27: 10000.0; R0603
R2: 1000.0; R0603
R3: 1600.5; R0603
R4: 4700.0; R0603
R15: 100000.0; R0603
R19: 220000.0; R0603
R20: 1000000.0; R0603
R23: 9100.0; R0603
R24: 680000.0; R0603
R25: 120000.0; R0603
R26: 2000.0; R0603
U1: STM32L152CBT6A; LQFP48
U2: AT25080B-SSHL-T; SOIC-8
U3: TST-110-05-T-D-RA
U4: LTC2804CGN-1#PBF; SSOP-16
U5: HTSS-105-01-G-D
U6: S25FL128SDPNFI001; WNG008
U7: 10118193-0001LF; FCI_10118193-0001LF
U8: prtr5v0u2ax; SOT143B
U9: ASEK-32.768KHz-ECST; ASEK
U10: ASFL1-25MHZ-NCS; ASFL1
U11: ltc3406es5; TSOT-23-5
U12: MCP73831T-2ACI/MC; DFN8_2X3MC
U13: S2B-PH-SM4-TB(LF)(SN); JST-2-SMD
U14: TPS3895ADRYR; SON-6
U15: 4-1437565-2; SW_4-1437565-2
U16: Q65110A2395; LGM67K-G1J2-24-Z
U17, U18: nc7sz125m5x; NC7SZ125M5X

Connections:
CLK_U1_3: U1.3, U9.3
CLK_U1_5: U1.5, U10.3
GND: C1.2, C2.2, C3.2, C4.2, C5.2, C6.2, C7.2, C8.2, C9.2, C10.2, C11.2, C12.2, C13.2, C15.2, C16.2, C17.2, C18.2, C19.2, C20.2, C21.1, C21.2, C22.2, C23.2, C24.2, C25.2, C26.2, R2.2, R5.2, R14.2, R19.2, R23.2, R25.2, R26.2, U1.8, U1.23, U1.35, U1.47, U2.4, U3.4, U3.6, U3.8, U3.10, U3.12, U3.14, U3.16, U3.18, U3.20, U4.8, U5.9, U6.4, U6.PAD, U7.5, U7.6, U7.7, U7.8, U7.9, U8.1, U9.2, U10.2, U11.2, U12.6, U12.9, U13.2, U14.2, U16.C, U17.2, U17.3, U18.1, U18.3
INPUT_USBPOWER_5V: C23.1, R27.2, U7.1, U8.4, U12.1, U12.2
NET_U1_1: C6.1, U1.1
NET_U1_7: R4.1, U1.7, U18.4
NET_U1_9: C7.1, C8.1, F1.1, U1.9
NET_U1_44: R5.1, U1.44
NET_U1_45: R3.1, U1.45, U16.A
NET_U1_46: R1.1, U1.46, U15.3, U15.4
NET_U2_3: R6.1, U2.3
NET_U2_7: R8.1, U2.7
NET_U3_19: R14.1, U3.19
NET_U4_6: C12.1, U4.6
NET_U4_7: C14.1, I1.2, U4.7
NET_U4_9: C13.1, U4.9
NET_U4_10: C14.2, U4.10
NET_U4_11: R15.1, U4.11
NET_U5_3: U4.1, U5.3
NET_U5_4: U4.2, U5.4
NET_U5_5: U4.3, U5.5
NET_U5_6: U4.4, U5.6
NET_U6_3: R16.1, U6.3
NET_U6_7: R18.1, U6.7
NET_U11_3: I2.1, U11.3
NET_U11_5: R19.1, R20.1, U11.5
NET_U11_ATNET_3: I2.2, R20.2
NET_U12_5: R27.1, U12.5
NET_U12_8: R26.1, U12.8
NET_U14_1: R22.1, R23.1, U14.1
NET_U14_3: R24.2, R25.1, U14.3
NET_U14_4: R21.1, U14.4, U17.4, U18.2
NET_U15_1: R2.1, U15.1, U15.2
PROC_SPI1_MISO: U1.16, U6.2
PROC_SPI1_MOSI: U1.17, U6.5
PROC_SPI1_NSS: R17.1, U1.14, U6.1
PROC_SPI1_SCK: U1.15, U6.6
PROC_SPI2_MISO: U1.27, U2.2
PROC_SPI2_MOSI: U1.28, U2.5
PROC_SPI2_NSS: R7.1, U1.25, U2.1
PROC_SPI2_SCK: U1.26, U2.6
PROC_SYS_JTCK_SWCLK: R12.1, U1.37, U3.9
PROC_SYS_JTDI: R10.1, U1.38, U3.5
PROC_SYS_JTDO_TRACESWO: U1.39, U3.13
PROC_SYS_JTMS_SWDIO: R11.1, U1.34, U3.7
PROC_SYS_JTRST: R9.1, U1.40, U3.3
PROC_USART2_CTS: U1.10, U4.13
PROC_USART2_RTS: U1.11, U4.15
PROC_USART2_RX: U1.13, U4.16
PROC_USART2_TX: U1.12, U4.14
PROC_USB_DM: U1.32, U7.2, U8.3
PROC_USB_DP: U1.33, U7.3, U8.2
RST_OUT_U3_SRESET_B: R13.1, U3.15, U17.1
VCC_S1_3V7: C20.1, C24.1, U11.4, U12.3, U12.4, U13.1
VCC_TIER1_3V3: C1.1, C2.1, C3.1, C4.1, C5.1, C9.1, C10.1, C11.1, C15.1, C16.1, C17.1, C18.1, C19.1, C21.2, C22.1, C25.1, C26.1, F1.2, I1.1, I2.2, R1.2, R3.2, R4.2, R6.2, R7.2, R8.2, R9.2, R10.2, R11.2, R12.2, R13.2, R15.2, R16.2, R17.2, R18.2, R20.2, R21.2, R22.2, R24.1, U1.24, U1.36, U1.48, U2.8, U3.1, U3.2, U4.5, U4.12, U6.8, U9.4, U10.4, U14.6, U17.5, U18.5
